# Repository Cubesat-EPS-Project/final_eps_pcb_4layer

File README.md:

# final_eps_pcb_4layer
Shifted to https://github.com/Cubesat-EPS-Project/Final_EPS_Version2

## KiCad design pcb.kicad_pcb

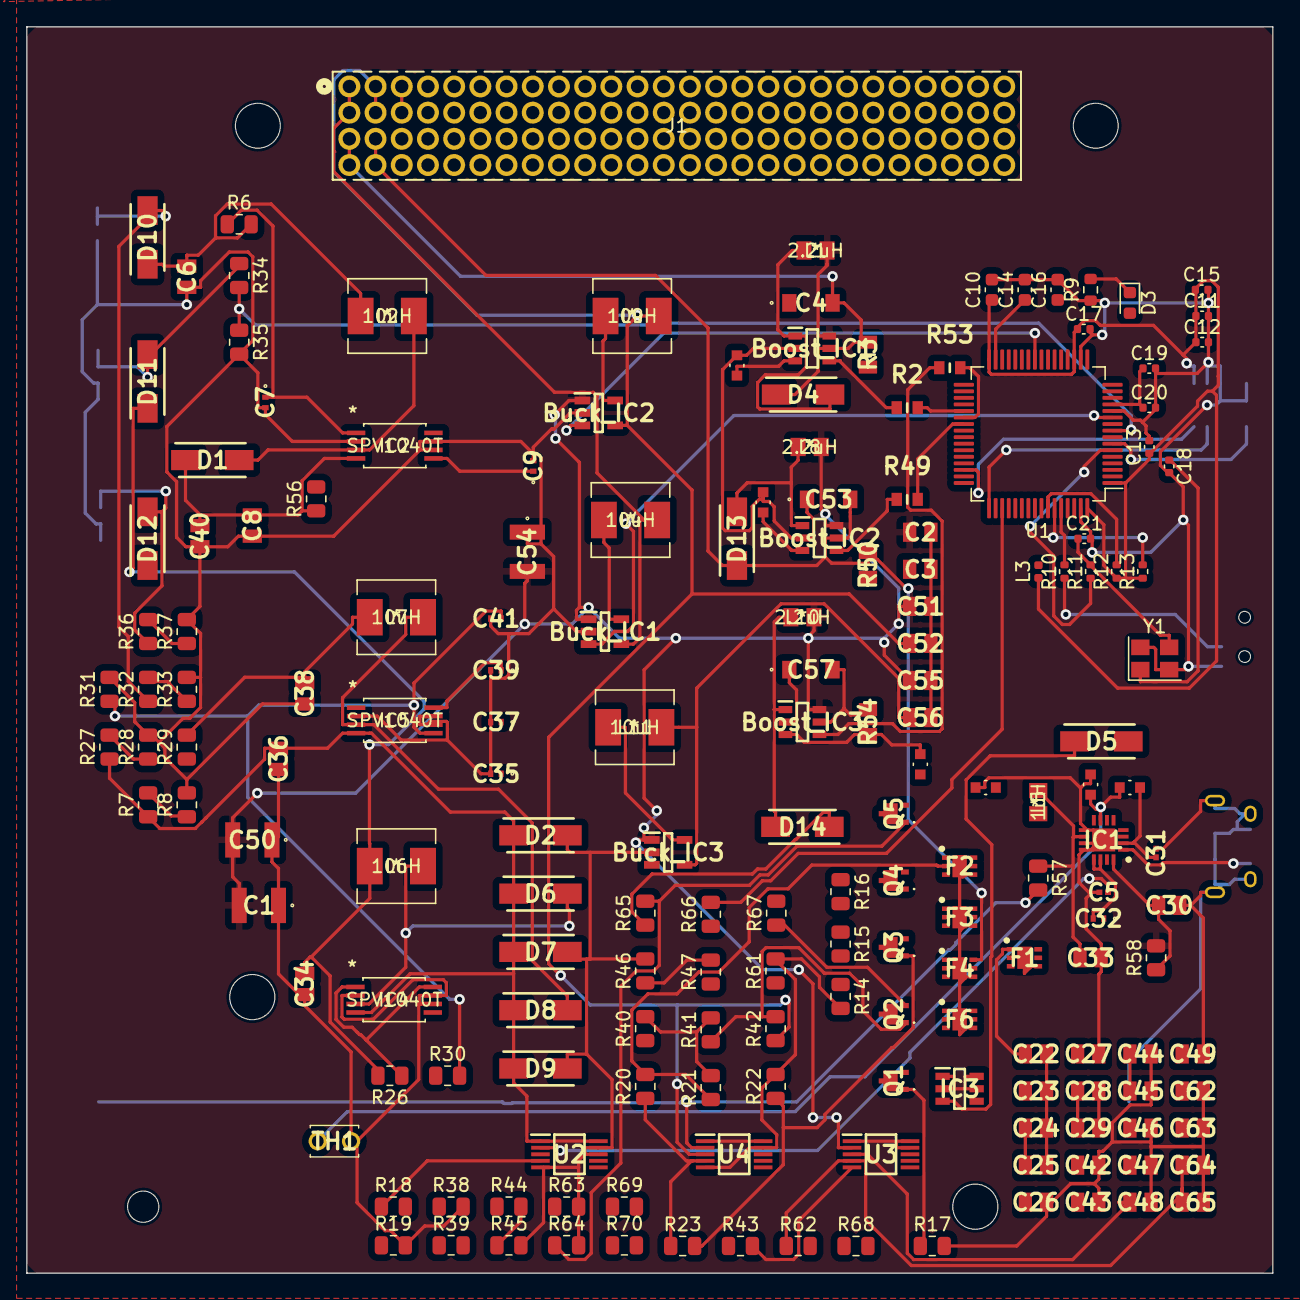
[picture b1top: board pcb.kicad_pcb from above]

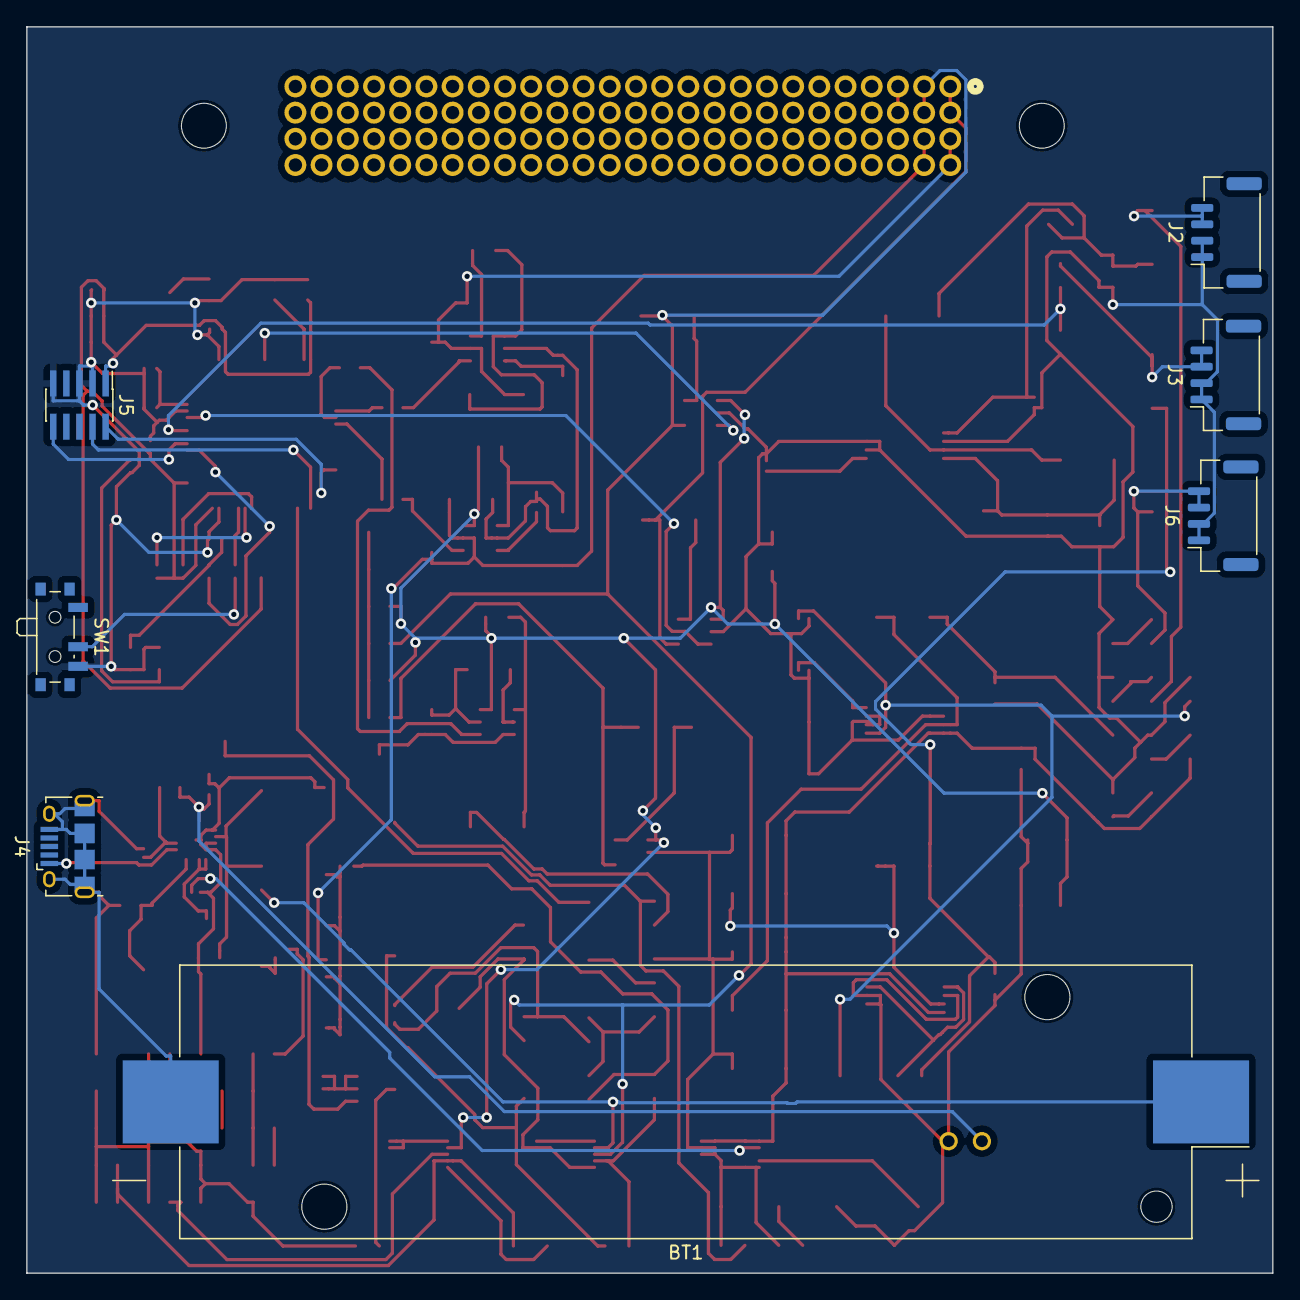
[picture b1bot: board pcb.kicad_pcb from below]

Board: 4 copper layers, 95.1 x 95.1 mm, 186 parts (7 on the bottom side), 108 nets.

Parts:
BT1: Battery_Cell; BatteryHolder_Keystone_1042_1x18650
Boost_IC1, Boost_IC2, Boost_IC3: LTC3426; SOT95P280X90-6N
Buck_IC1, Buck_IC2, Buck_IC3: TPS62203DBVT; SOT95P280X145-5N
C1, C50, C54: 4.7uF; C1210
C2, C3, C6, C22, C26, C30, C33, C34, C38, C42, C46, C51, C52, C55, C56, C62: 10uF; CAPC2012X94N
C4, C53, C57: 22uF; C3216_Commercial
C5, C31: 2.2uF; CAPC0603X33N
C7, C9, C35, C37, C39, C41: 1nF; C1005_Commercial
C8, C36, C40: 22uF; CAPC2012X94N
C10: 4u7; C_0603_1608Metric
C11, C12, C13, C15, C17: 100n; C_0402_1005Metric
C14, C16: 2u2; C_0603_1608Metric
C18, C21: 12p; C_0402_1005Metric
C19: 1u; C_0402_1005Metric
C20: 10n; C_0402_1005Metric
C23, C27, C43, C47, C63: 100pF; CAPC2012X94N
C24, C28, C44, C48, C64: 100nF; CAPC2012X94N
C25, C29, C45, C49, C65: 1uF; CAPC2012X94N
C32: 47nF; C1005_Commercial
D1, D4, D5, D6, D8, D13, D14: STPS2150A; DIOM5126X265N
D2, D7, D9: SMM4F5.0A-TR; DIOM5126X265N
D3: BLUE; LED_0603_1608Metric
D10, D11, D12: D_Schottky; DIOM5126X265N
F1, F2, F3, F4, F6: TPS25961DRVR; SON65P200X200X80-7N
IC1: BQ25302RTER; QFN50P300X300X80-17N-D
IC2, IC4, IC5: SPV1040T
IC3: SI3483DDV-T1-BE3; SOT95P284X110-6N
J1: PTHF-126-02-GF-Q-368; CONN_PTHF-126-02-GF-Q-368_SAI
J2: Sol_X+_X-; JST_GH_SM04B-GHS-TB_1x04-1MP_P1.25mm_Horizontal
J3: Sol_Y+_Y-; JST_GH_SM04B-GHS-TB_1x04-1MP_P1.25mm_Horizontal
J4: USB_B_Micro; USB_Micro-B_Amphenol_10118194_Horizontal
J5: SWD; PinHeader_2x05_P1.00mm_Vertical_SMD
J6: Sol_Z+_Z-; JST_GH_SM04B-GHS-TB_1x04-1MP_P1.25mm_Horizontal
L1, L8, L10: 2.2uH; IHHP0805ZHER1R0M01
L2, L4, L6, L7, L9, L11: 10uH; IHLP2020CZER2R2M8A
L3: 39n; L_0402_1005Metric
L5: 1uH; IHHP0805ZHER1R0M01
Q1, Q2, Q3, Q4, Q5: NPN; PBSS4310PASQX
R2, R49, R53: 1M; RESC1608X55N
R3, R50, R54: 95.3k; RESC2012X60N
R4, R5, R51, R55: 30.9k; RC0603FR-0730K9L
R6, R26, R29: 1k; R_0805_2012Metric
R7, R27, R30: 390k; R_0805_2012Metric
R8, R28, R31: 130k; R_0805_2012Metric
R9: 1k5; R_0603_1608Metric
R10: 10k; R_0402_1005Metric
R11: 47; R_0402_1005Metric
R12, R13: 2k2; R_0402_1005Metric
R14, R32, R33, R34, R35, R36, R37, R38: 100k; R_0805_2012Metric
R15, R18, R20, R23, R39, R42, R44, R47, R62, R65: 2M; R_0805_2012Metric
R16, R40: 953k; R_0805_2012Metric
R17, R41: 1.54M; R_0805_2012Metric
R19, R43, R61: 50.5k; R_0805_2012Metric
R21, R45, R63: 549k; R_0805_2012Metric
R22, R46, R64: 787k; R_0805_2012Metric
R24: 4.52k; RC0603FR-0730K9L
R25: 23.6k; RC0603FR-0730K9L
R56, R57, R58, R66, R67, R68, R69, R70: 50m; R_0805_2012Metric
SW1: SW_SPDT; SW_SPDT_PCM12
TH1: Thermistor; 103AT2
U1: STM32F405RGT6; LQFP-64_10x10mm_P0.5mm
U2, U3, U4: LTC2990; SOP50P490X110-10N
Y1: 16MHz; Crystal_SMD_3225-4Pin_3.2x2.5mm

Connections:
3.3V_ADCS: Buck_IC2.4 (FB), C44.1, C45.1, C52.1, F3.6 (IN), J1.5, J1.6, L9.2, R39.1, R42.1, U4.3 (V3)
3.3V_ADCS_EN: R67.2, U1.40 (PC9)
3.3V_COMM: Buck_IC3.4 (FB), C24.1, C25.1, C56.1, F1.6 (IN), J1.9, J1.10, L11.2, R15.1, R18.1, U2.4 (V4)
3.3V_COMM_EN: R66.2, U1.51 (PC10)
3.3Vout_ADCS: C42.1, F3.1 (OUT)
3.3Vout_COMM: C22.1, F1.1 (OUT)
5V: Boost_IC1.5 (VOUT), C4.2, D4.1 (K), J1.3, J1.4, R3.2
5V_COMM: Boost_IC3.5 (VOUT), C57.2, C64.1, C65.1, D14.1 (K), F6.6 (IN), R54.2, R62.1, R65.1, U3.4 (V4)
5V_OBC: C28.1, C29.1, F2.6 (IN), R20.1, R23.1, U4.4 (V4)
5V_OBC_EN: R68.2, U1.52 (PC11)
5V_PAYLOAD: Boost_IC2.5 (VOUT), C48.1, C49.1, C53.2, D13.1 (K), F4.6 (IN), J1.7, J1.8, R44.1, R47.1, R50.2, U3.3 (V3)
5V_PAYLOAD_EN: R69.2, U1.2 (PC13)
5Vout_COMM: C62.1, F6.1 (OUT)
5Vout_OBC: C26.1, F2.1 (OUT)
5Vout_PAYLOAD: C46.1, F4.1 (OUT)
+3.3V: Buck_IC1.4 (FB), C3.1, J1.1, J1.2, L4.2
+3.3VA: C19.1, C20.1, L3.2, U1.13 (VDDA)
+3V3: C10.1, C11.1, C12.1, C13.1, C15.1, C17.1, J5.1, L3.1, R12.1, R13.1, SW1.1 (A), U1.1 (VBAT), U1.19 (VDD), U1.32 (VDD), U1.48 (VDD), U1.64 (VDD)
+Vpp: Boost_IC1.6 (VIN), Boost_IC2.6 (VIN), Boost_IC3.6 (VIN), Buck_IC1.1 (VI), Buck_IC2.1 (VI), Buck_IC3.1 (VI), C1.2, C2.1, C50.2, C51.1, C54.2, C55.1, L1.1, L8.1, L10.1, R58.2, U3.2 (V2)
BATTCH_EN: IC1.6 (~EN), U1.27 (PB1)
BAT_I+: C33.1, IC1.10 (BAT), IC3.1 (D_1), IC3.2 (D_2), IC3.5 (D_3), IC3.6 (D_4), L5.2, R57.1, U4.1 (V1), U4.8 (ADR0), U4.10 (VCC)
BAT_I-: BT1.1 (+), R57.2, U4.2 (V2)
BOOST_SHDN_COMM: R53.2, U1.38 (PC7)
BOOST_SHDN_OBC: R2.2, U1.37 (PC6)
BOOST_SHDN_PAYLOAD: R49.2, U1.39 (PC8)
BOOT0: R10.2, U1.60 (BOOT0)
BUCK_EN_ADCS: Buck_IC2.3 (EN), U1.25 (PC5)
BUCK_EN_COMM: Buck_IC3.3 (EN), U1.24 (PC4)
BUCK_EN_STM32: Buck_IC1.3 (EN), U1.11 (PC3)
Earth: BT1.2 (-), Boost_IC1.2 (GND), Boost_IC2.2 (GND), Boost_IC3.2 (GND), Buck_IC1.2 (GND), Buck_IC2.2 (GND), Buck_IC3.2 (GND), C1.1, C2.2, C3.2, C4.1, C5.2, C6.2, C7.2, C8.2, C9.2, C22.2, C23.2, C24.2, C25.2, C26.2, C27.2, C28.2, C29.2, C30.2, C31.2, C33.2, C34.2, C35.2, C36.2, C37.2, C38.2, C39.2, C40.2, C41.2, C42.2, C43.2, C44.2, C45.2, C46.2, C47.2, C48.2, C49.2, C50.1, C51.2, C52.2, C53.1, C54.1, C55.2, C56.2, C57.1, C62.2, C63.2, C64.2, C65.2, D2.2 (A), D7.2 (A), D9.2 (A), F1.4 (GND_1), F1.7 (GND_2), F2.4 (GND_1), F2.7 (GND_2), F3.4 (GND_1), F3.7 (GND_2), F4.4 (GND_1), F4.7 (GND_2), F6.4 (GND_1), F6.7 (GND_2), IC1.9 (VSET), IC1.11 (GND_1), IC1.12 (GND_2), IC1.17 (EP), IC2.2 (GND), IC2.6 (ICTRL_MINUS), IC2.7 (ICTRL_PLUS), IC4.2 (GND), IC4.6 (ICTRL_MINUS), IC4.7 (ICTRL_PLUS), IC5.2 (GND), IC5.6 (ICTRL_MINUS), IC5.7 (ICTRL_PLUS), J2.1, J2.2, J3.1, J3.2, J4.5 (GND), J4.6 (Shield), J6.1, J6.2, Q1.3 (E), Q2.3 (E), Q3.3 (E), Q4.3 (E), Q5.3 (E), R4.1, R5.1, R8.2, R14.2, R16.2, R17.2, R19.2, R21.2, R22.2, R25.1, R28.2, R31.2, R33.2, R35.2, R37.2, R38.2, R40.2, R41.2, R43.2, R45.2, R46.2, R51.1, R55.1, R61.2, R63.2, R64.2, TH1.2, U2.5 (GND), U2.8 (ADR0), U2.9 (ADR1), U3.5 (GND), U3.8 (ADR0), U4.5 (GND), U4.9 (ADR1)
GND: C10.2, C11.2, C12.2, C13.2, C14.2, C15.2, C16.2, C17.2, C18.2, C19.2, C20.2, C21.2, J5.3, J5.5, J5.9, R9.1, SW1.3 (C), U1.12 (VSSA), U1.18 (VSS), U1.63 (VSS), Y1.2, Y1.4
HSE_IN: C18.1, U1.5 (PH0), Y1.1
HSE_OUT: R11.1, U1.6 (PH1)
I2C1_SCL: R12.2, U1.58 (PB6), U2.7 (SCL), U3.7 (SCL), U4.7 (SCL)
I2C1_SDA: R13.2, U1.59 (PB7), U2.6 (SDA), U3.6 (SDA), U4.6 (SDA)
LED_STATUS: D3.2 (A), U1.21 (PA5)
MPPT_I+: C8.1, C36.1, C40.1, D1.1 (K), D2.1 (K), D6.1 (K), D7.1 (K), D8.1 (K), D9.1 (K), IC2.4 (VOUT), IC4.4 (VOUT), IC5.4 (VOUT), R7.1, R27.1, R30.1, R56.1, U2.1 (V1), U2.10 (VCC)
MPPT_I-: C5.1, D5.2 (A), IC1.1 (VBUS), J4.1 (VBUS), R56.2, U2.2 (V2)
NRST: J5.10, U1.7 (NRST)
unnamed: Boost_IC1.3 (FB), R3.1, R4.2
unnamed: Boost_IC1.1 (SW), D4.2 (A), L1.2
unnamed: Boost_IC1.4 (~SHDN), R2.1
unnamed: Boost_IC2.3 (FB), R50.1, R51.2
unnamed: Boost_IC2.1 (SW), D13.2 (A), L8.2
unnamed: Boost_IC2.4 (~SHDN), R49.1
unnamed: Boost_IC3.3 (FB), R54.1, R55.2
unnamed: Boost_IC3.1 (SW), D14.2 (A), L10.2
unnamed: Boost_IC3.4 (~SHDN), R53.1
unnamed: Buck_IC1.5 (SW), L4.1
unnamed: Buck_IC2.5 (SW), L9.1
unnamed: Buck_IC3.5 (SW), L11.1
unnamed: C21.1, R11.2, Y1.3
unnamed: D1.2 (A), IC2.3 (LX), L2.2
unnamed: D3.1 (K), R9.2
unnamed: D5.1 (K), IC3.3 (G)
unnamed: D6.2 (A), IC4.3 (LX), L6.2
unnamed: D8.2 (A), IC5.3 (LX), L7.2
unnamed: D10.2 (A), J2.3, J2.4, R32.1
unnamed: C6.1, D10.1 (K), L2.1, R6.2
unnamed: D11.2 (A), J3.3, J3.4, R34.1
unnamed: C34.1, D11.1 (K), L6.1, R26.2
unnamed: D12.2 (A), J6.3, J6.4, R36.1
unnamed: C38.1, D12.1 (K), L7.1, R29.2
unnamed: C23.1, F1.5 (EN/UVLO), Q1.1 (C), R17.1, R18.2
unnamed: F1.3 (ILIM), R14.1
unnamed: F1.2 (OVLO), R15.2, R16.1
unnamed: C27.1, F2.5 (EN/UVLO), Q3.1 (C), R22.1, R23.2
unnamed: F2.3 (ILIM), R19.1
unnamed: F2.2 (OVLO), R20.2, R21.1
unnamed: C43.1, F3.5 (EN/UVLO), Q2.1 (C), R41.1, R42.2
unnamed: F3.3 (ILIM), R38.1
unnamed: F3.2 (OVLO), R39.2, R40.1
unnamed: C47.1, F4.5 (EN/UVLO), Q4.1 (C), R46.1, R47.2
unnamed: F4.3 (ILIM), R43.1
unnamed: F4.2 (OVLO), R44.2, R45.1
unnamed: C63.1, F6.5 (EN/UVLO), Q5.1 (C), R64.1, R65.2
unnamed: F6.3 (ILIM), R61.1
unnamed: F6.2 (OVLO), R62.2, R63.1
unnamed: C32.1, IC1.15 (BTST)
unnamed: IC1.4 (ICHG), R5.2
unnamed: C30.1, IC1.16 (PMID), IC3.4 (S), R58.1
unnamed: C32.2, IC1.13 (SW_1), IC1.14 (SW_2), L5.1
unnamed: IC1.7 (TS), R24.1, R25.2, TH1.1
unnamed: C7.1, IC2.1 (MPP-SET), IC2.8 (XSHUT), R6.1
unnamed: C9.1, IC2.5 (VCTRL), R7.2, R8.1
unnamed: C35.1, IC4.1 (MPP-SET), IC4.8 (XSHUT), R26.1
unnamed: C37.1, IC4.5 (VCTRL), R27.2, R28.1
unnamed: C39.1, IC5.1 (MPP-SET), IC5.8 (XSHUT), R29.1
unnamed: C41.1, IC5.5 (VCTRL), R30.2, R31.1
unnamed: Q1.2 (B), R66.1
unnamed: Q2.2 (B), R67.1
unnamed: Q3.2 (B), R68.1
unnamed: Q4.2 (B), R69.1
unnamed: Q5.2 (B), R70.1
unnamed: R10.1, SW1.2 (B)
unnamed: C14.1, U1.31 (VCAP_1)
unnamed: C16.1, U1.47 (VCAP_2)
REGN: C31.1, IC1.2 (REGN), R24.2
SOL_X_ADC: R32.2, R33.1, U1.8 (PC0)
SOL_Y_ADC: R34.2, R35.1, U1.9 (PC1)
SOL_Z_ADC: R36.2, R37.1, U1.10 (PC2)
STAT: IC1.3 (STAT), U1.26 (PB0)
SWCLK: J5.4, U1.49 (PA14)
SWDIO: J5.2, U1.46 (PA13)
SWO: J5.6, U1.55 (PB3)
USB_D+: J4.3 (D+), U1.45 (PA12)
USB_D-: J4.2 (D-), U1.44 (PA11)
Vpp_I+: U3.1 (V1), U3.9 (ADR1), U3.10 (VCC)

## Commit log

2023-05-05 INIT
2023-05-07 added MPPT & STM32
    added spv1040t mppt circuit and stm32f405 chip with its bare minimum components and labelling required pinouts.
2023-05-07 Added protection circuit
    added protection citcuit with tps25961 ic for 3.3V and 5V bus.
2023-05-13 Major
2023-05-24 Final Schematic
    Final Schematic. PC104 pins not assigned.
2023-05-24 Ready to rearrange
2023-05-24 Arranged
2023-05-24 LIBS + 3D EXPORT, Ready to reroute

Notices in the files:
parts and their libraries:
Copyright 2021 Accelerated Designs. All rights reserved.
